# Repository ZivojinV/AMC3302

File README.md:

# AMC3302-Based Precision Full-Wave Rectifier PCB

## Description
Custom AMC3302-based full-wave rectifier PCB for AC signal measurement and conditioning.

## Overview
The input AC signal is measured using the AMC3302 isolated amplifier and further processed through a dual MCP6022 stage to produce a full-wave rectified output.

The system was iteratively tested and validated through signal measurement and analysis to ensure correct behavior and stable output.

## Hardware
- Custom PCB design  
- AMC3302 isolated amplifier  
- Dual MCP6022 operational amplifiers  
- LM78L05 voltage regulator  

**Images:**

- Empty PCB  

- Assembled PCB  

## Results
Signal verification through measurement:

- Input signal  

- Rectified output signal  

- Input vs Output comparison  

## Status
- Designed and assembled  
- Tested and validated through measurement  
- Functionality confirmed  

## Notes
Additional capacitors were introduced after testing to reduce noise and improve output signal stability.

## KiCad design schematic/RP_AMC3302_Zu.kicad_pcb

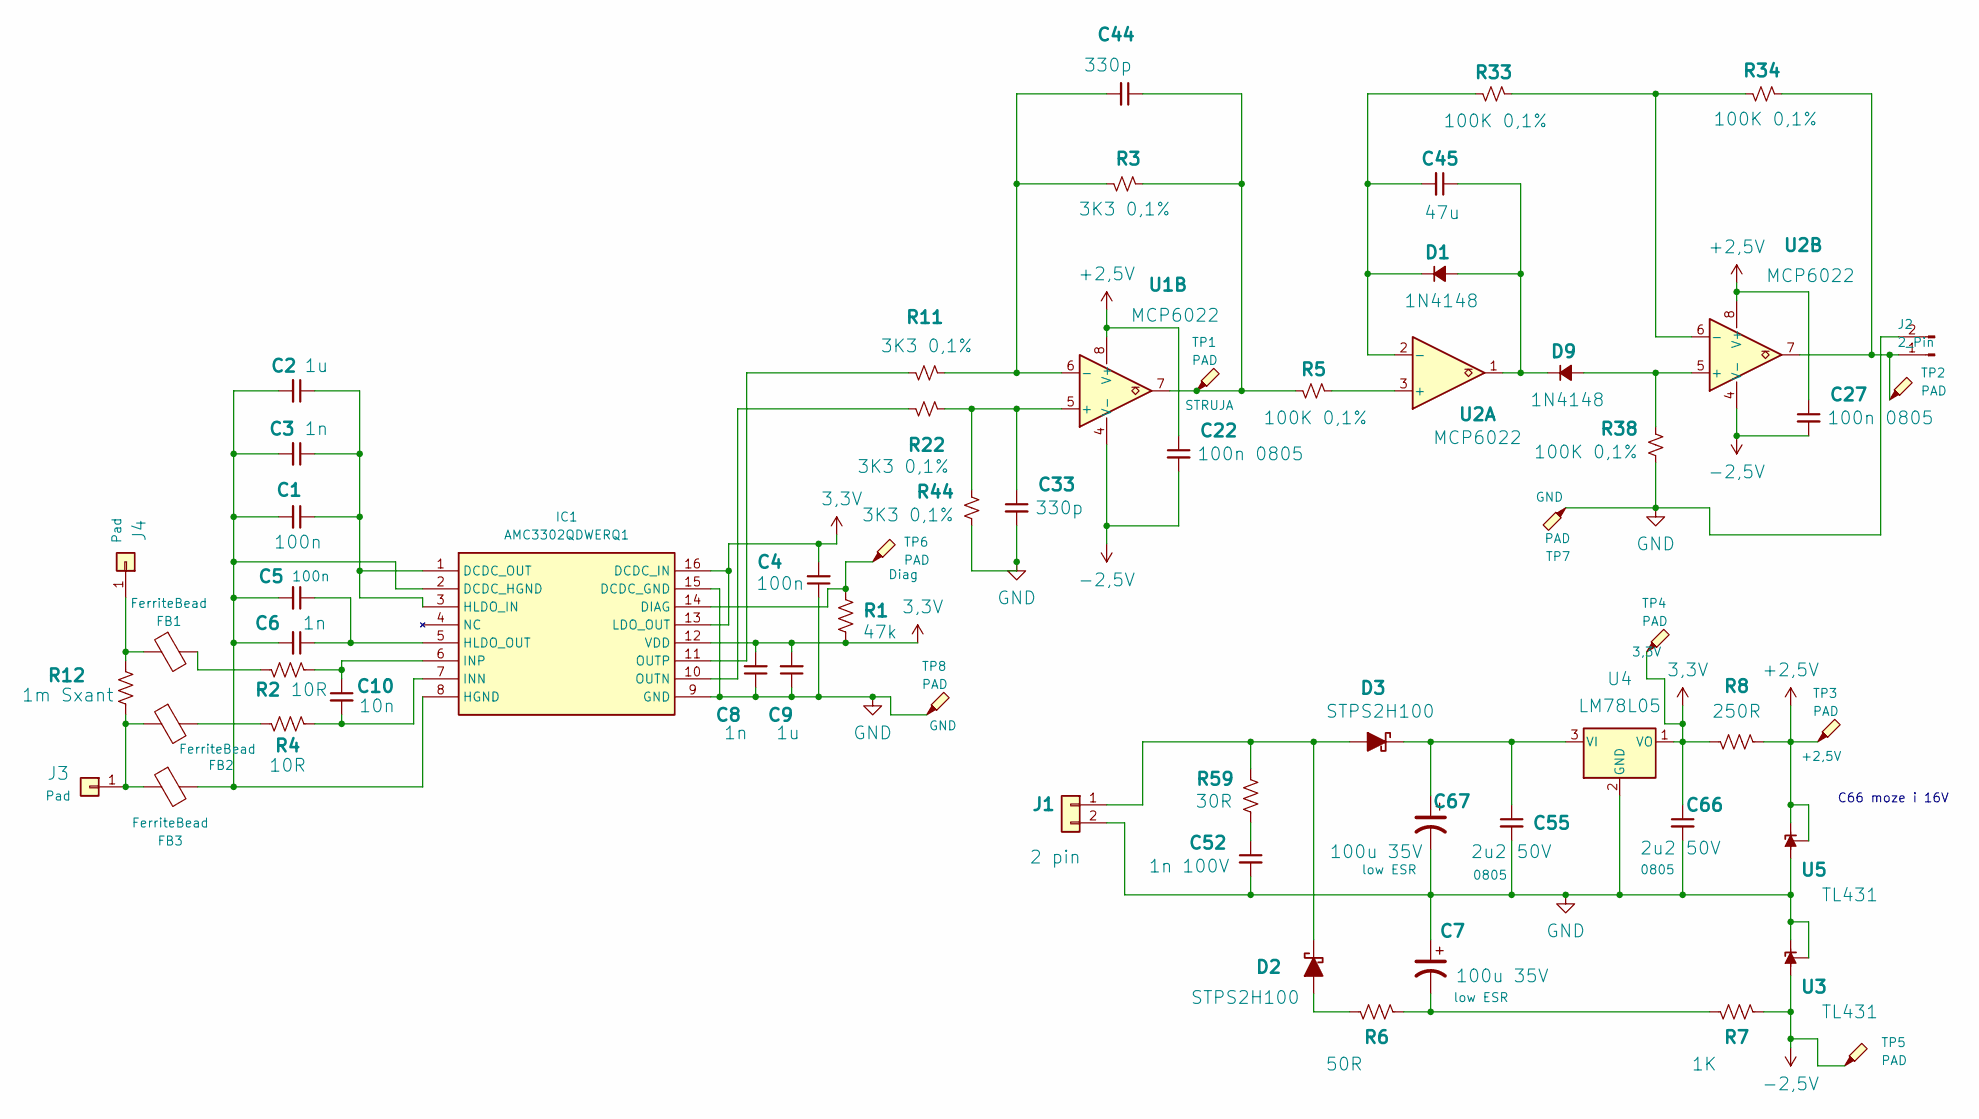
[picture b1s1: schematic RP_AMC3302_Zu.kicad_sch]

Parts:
C1, C4, C5: 100n; C_0603_1608Metric_Pad1.08x0.95mm_HandSolder
C2: 1u; C_0603_1608Metric_Pad1.08x0.95mm_HandSolder
C3, C6: 1n; C_0603_1608Metric_Pad1.08x0.95mm_HandSolder
C7, C67: 100u 35V; CP_Radial_D8.0mm_P3.50mm
C8: 1n; C_1206_3216Metric_Pad1.33x1.80mm_HandSolder
C9: 1u; C_1206_3216Metric_Pad1.33x1.80mm_HandSolder
C10: 10n; C_0603_1608Metric
C22, C27: 100n 0805; C_0805_2012Metric_Pad1.18x1.45mm_HandSolder
C33, C44: 330p; C_Disc_D5.0mm_W2.5mm_P5.00mm
C45: 47u; C_Disc_D5.0mm_W2.5mm_P5.00mm
C52: 1n 100V; C_Disc_D5.0mm_W2.5mm_P5.00mm
C55, C66: 2u2 50V; C_0805_2012Metric_Pad1.18x1.45mm_HandSolder
D1, D9: 1N4148; D_DO-35_SOD27_P7.62mm_Horizontal
D2, D3: STPS2H100; D_DO-41_SOD81_P10.16mm_Horizontal
FB1, FB2, FB3: FerriteBead; L_0402_1005Metric_Pad0.77x0.64mm_HandSolder
IC1: AMC3302QDWERQ1; SOIC127P1030X265-16N; Manufacturer_Part_Number AMC3302QDWERQ1; Mouser Part Number 595-AMC3302QDWERQ1
J1: 2 pin; SHDR2W125P0X396_1X2_620X890X1700P
J2: 2_Pin; PinHeader_1x02_P2.54mm_Vertical
J3, J4: Pad; SolderWire-1.5sqmm_1x01_D1.7mm_OD3.9mm
R1: 47k; R_0603_1608Metric
R2, R4: 10R; R_0603_1608Metric
R3, R11, R22, R44: 3K3 0,1%; R_Axial_DIN0207_L6.3mm_D2.5mm_P10.16mm_Horizontal
R5, R33, R34, R38: 100K 0,1%; R_Axial_DIN0207_L6.3mm_D2.5mm_P10.16mm_Horizontal
R6: 50R; R_0805_2012Metric_Pad1.20x1.40mm_HandSolder
R7: 1K; R_0805_2012Metric_Pad1.20x1.40mm_HandSolder
R8: 250R; R_0805_2012Metric_Pad1.20x1.40mm_HandSolder
R12: 1m Sxant; R_2512_6332Metric
R59: 30R; R_Axial_DIN0207_L6.3mm_D2.5mm_P10.16mm_Horizontal
TP1, TP2, TP3, TP4, TP5, TP6: PAD; TestPoint_THTPad_D1.5mm_Drill0.7mm
TP7, TP8: PAD; TestPoint_Loop_D2.50mm_Drill1.85mm
U1, U2: MCP6022; DIP-8_W7.62mm
U3, U5: TL431; TO-92
U4: LM78L05; TO-92_Inline

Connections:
3,3V: C4.2, C8.2, C9.2, C66.1, IC1.12 (VDD), IC1.13 (LDO_OUT), IC1.16 (DCDC_IN), R1.2, R8.2, TP4.1, U4.1 (VO)
+2,5V: C22.1, C27.1, R8.1, TP3.1, U1.8 (V+), U2.8 (V+), U5.1 (REF), U5.3 (K)
-2,5V: C22.2, C27.2, R7.1, TP5.1, U1.4 (V-), U2.4 (V-), U3.2 (A)
GND: C4.1, C7.1, C8.1, C9.1, C33.2, C52.2, C55.2, C66.2, C67.2, IC1.9 (GND), IC1.15 (DCDC_GND), J1.2, J2.2, R38.1, R44.1, TP7.1, TP8.1, U3.1 (REF), U3.3 (K), U4.2 (GND), U5.2 (A)
unnamed: C7.2, R6.1, R7.2
unnamed: C44.1, R3.1, R5.2, TP1.1, U1.7
unnamed: C52.1, R59.2
unnamed 7: C45.1, D1.2 (A), D9.1 (K), U2.1; also elsewhere on the board
unnamed: C45.2, D1.1 (K), R33.2, U2.2 (-)
unnamed: D2.2 (A), R6.2
unnamed: D2.1 (K), D3.2 (A), J1.1, R59.1
unnamed: C55.1, C67.1, D3.1 (K), U4.3 (VI)
unnamed: D9.2 (A), R38.2, U2.5 (+)
unnamed: FB1.2, R2.2
unnamed: FB2.2, R4.2
unnamed: C1.2, C2.2, C3.2, C5.2, C6.2, FB3.2, IC1.2 (DCDC_HGND), IC1.8 (HGND)
unnamed: C1.1, C2.1, C3.1, IC1.1 (DCDC_OUT), IC1.3 (HLDO_IN)
unnamed: IC1.14 (DIAG), R1.1, TP6.1
unnamed: C5.1, C6.1, IC1.5 (HLDO_OUT)
unnamed: C10.2, IC1.7 (INN), R4.1
unnamed: C10.1, IC1.6 (INP), R2.1
unnamed: IC1.10 (OUTN), R22.2
unnamed: IC1.11 (OUTP), R11.2
unnamed: J2.1, R34.1, TP2.1, U2.7
unnamed: FB2.1, FB3.1, J3.1, R12.2
unnamed: FB1.1, J4.1, R12.1
unnamed: C33.1, R22.1, R44.2, U1.5 (+)
unnamed: C44.2, R3.2, R11.1, U1.6 (-)
unnamed: R5.1, U2.3 (+)
unnamed 29: R33.1, R34.2, U2.6 (-); also elsewhere on the board

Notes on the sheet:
C66 moze i 16V

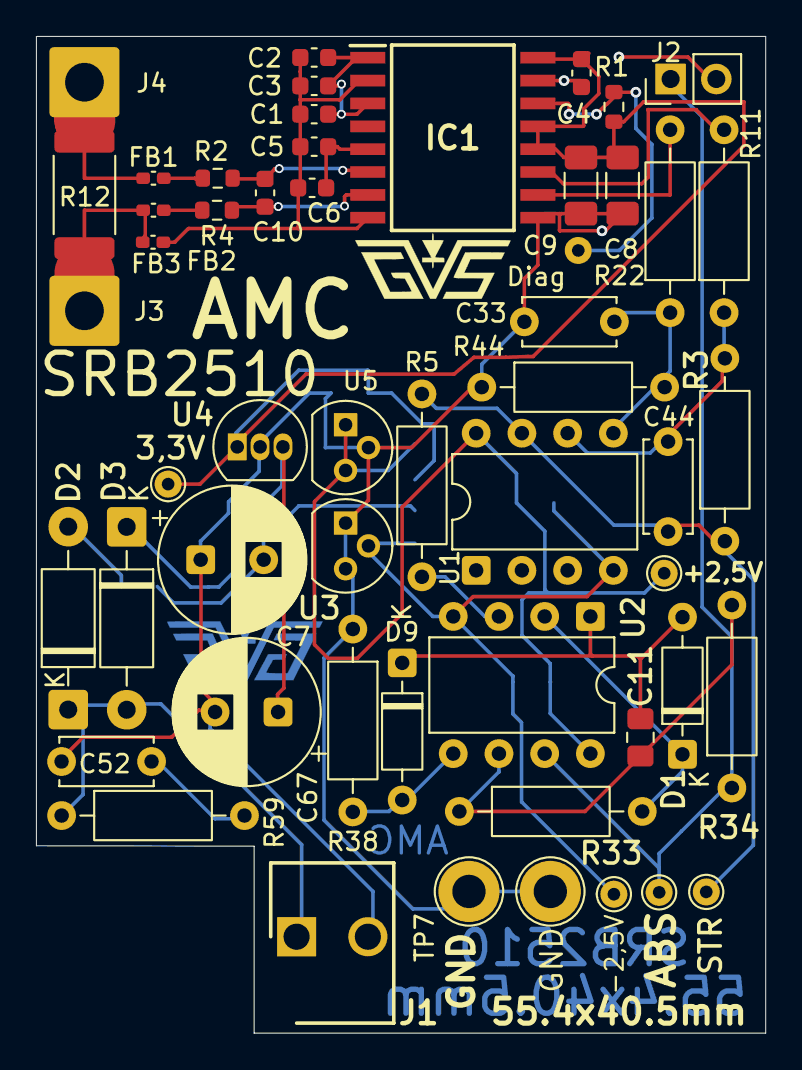
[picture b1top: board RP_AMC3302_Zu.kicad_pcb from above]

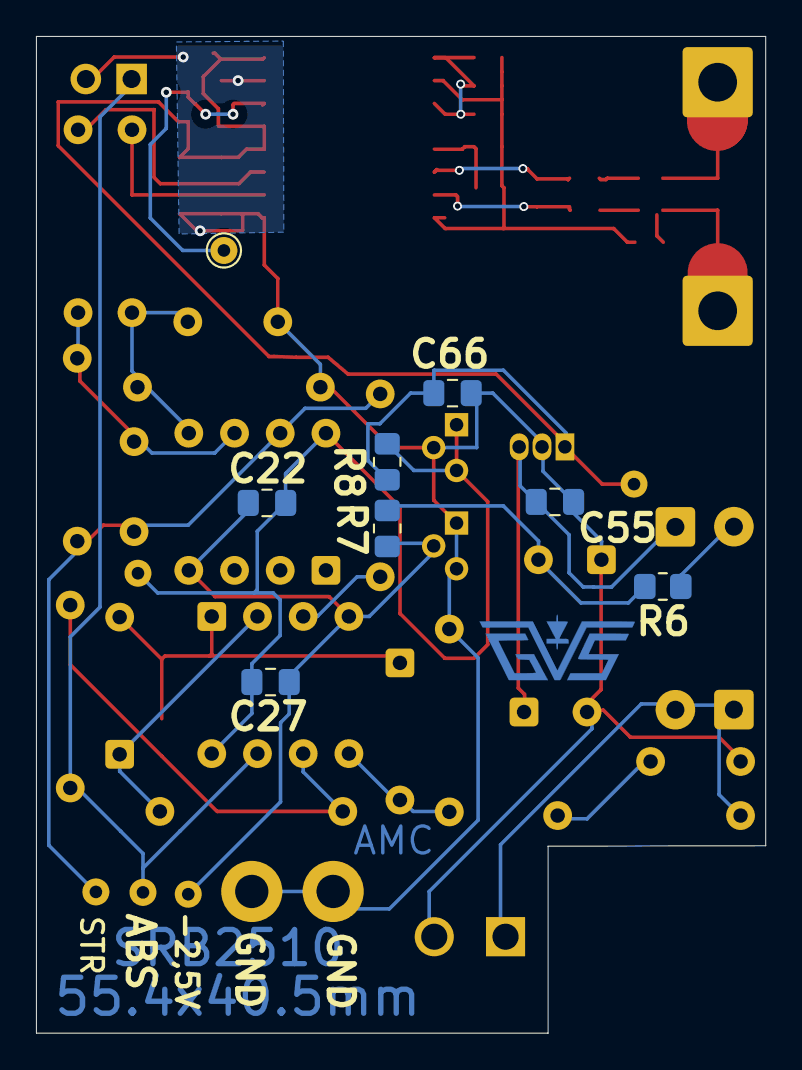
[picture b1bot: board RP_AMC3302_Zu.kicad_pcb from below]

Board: 2 copper layers, 40.5 x 55.4 mm, 62 parts (9 on the bottom side), 30 nets.

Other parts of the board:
C11: 10p 0805; C_0805_2012Metric_Pad1.18x1.45mm_HandSolder
H1: GVS logo; gvslogo_mali_Cu
H2: GVS logo; gvslogo_mali

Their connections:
unnamed 7: C11.2; also elsewhere on the board
unnamed 29: C11.1; also elsewhere on the board

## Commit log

2026-04-17 Create schematic
2026-04-18 Rename Input i output.jpeg to Input_output.jpeg
2026-04-18 Rename Input signal.jpeg to Input_signal.jpeg
2026-04-18 Rename Output signal.jpeg to Output_signal.jpeg
2026-04-18 Rename Prazna ploca prednja strana.jpg to Prazna_prednja.jpg
2026-04-18 Rename Prednja sastavljena.jpeg to Prednja_sastavljena.jpeg
2026-04-18 Rename Zadnja popunjena.jpeg to Zadnja_popunjena.jpeg
2026-04-18 Rename Prazna zadnja strana.jpeg to Prazna_zadnja.jpeg
